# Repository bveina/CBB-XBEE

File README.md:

CBB-XBEE
========

This repository contains the design files for the Logic Supply CBB-XBEE Cape for the 
BeagleBone and BeagleBone Black. It's a general prototyping cape with a footprint to connect a XBee or
other compatible radio module.

The CBB-XBEE Cape is available at http://www.logicsupply.com/components/beaglebone/capes/cbb-xbee/

Check out the CBB-XBEE manual at https://docs.google.com/document/d/1f1zFzsrbu90K2d8ETkYjHSfjAa8HdVvbnBUYrnl4jPE/edit?usp=sharing

----

Follow us on Google+ for updates and more information: https://plus.google.com/u/0/b/103613886667848850929/

Created by Alexander Hiam for Logic Supply.

This work is licensed under the Creative Commons Attribution-Share Alike 3.0 Unported License. 
To view a copy of this license, visit http://creativecommons.org/licenses/by-sa/3.0/ or send a 
letter to Creative Commons, 171 Second Street, Suite 300, San Francisco, California, 94105, USA.

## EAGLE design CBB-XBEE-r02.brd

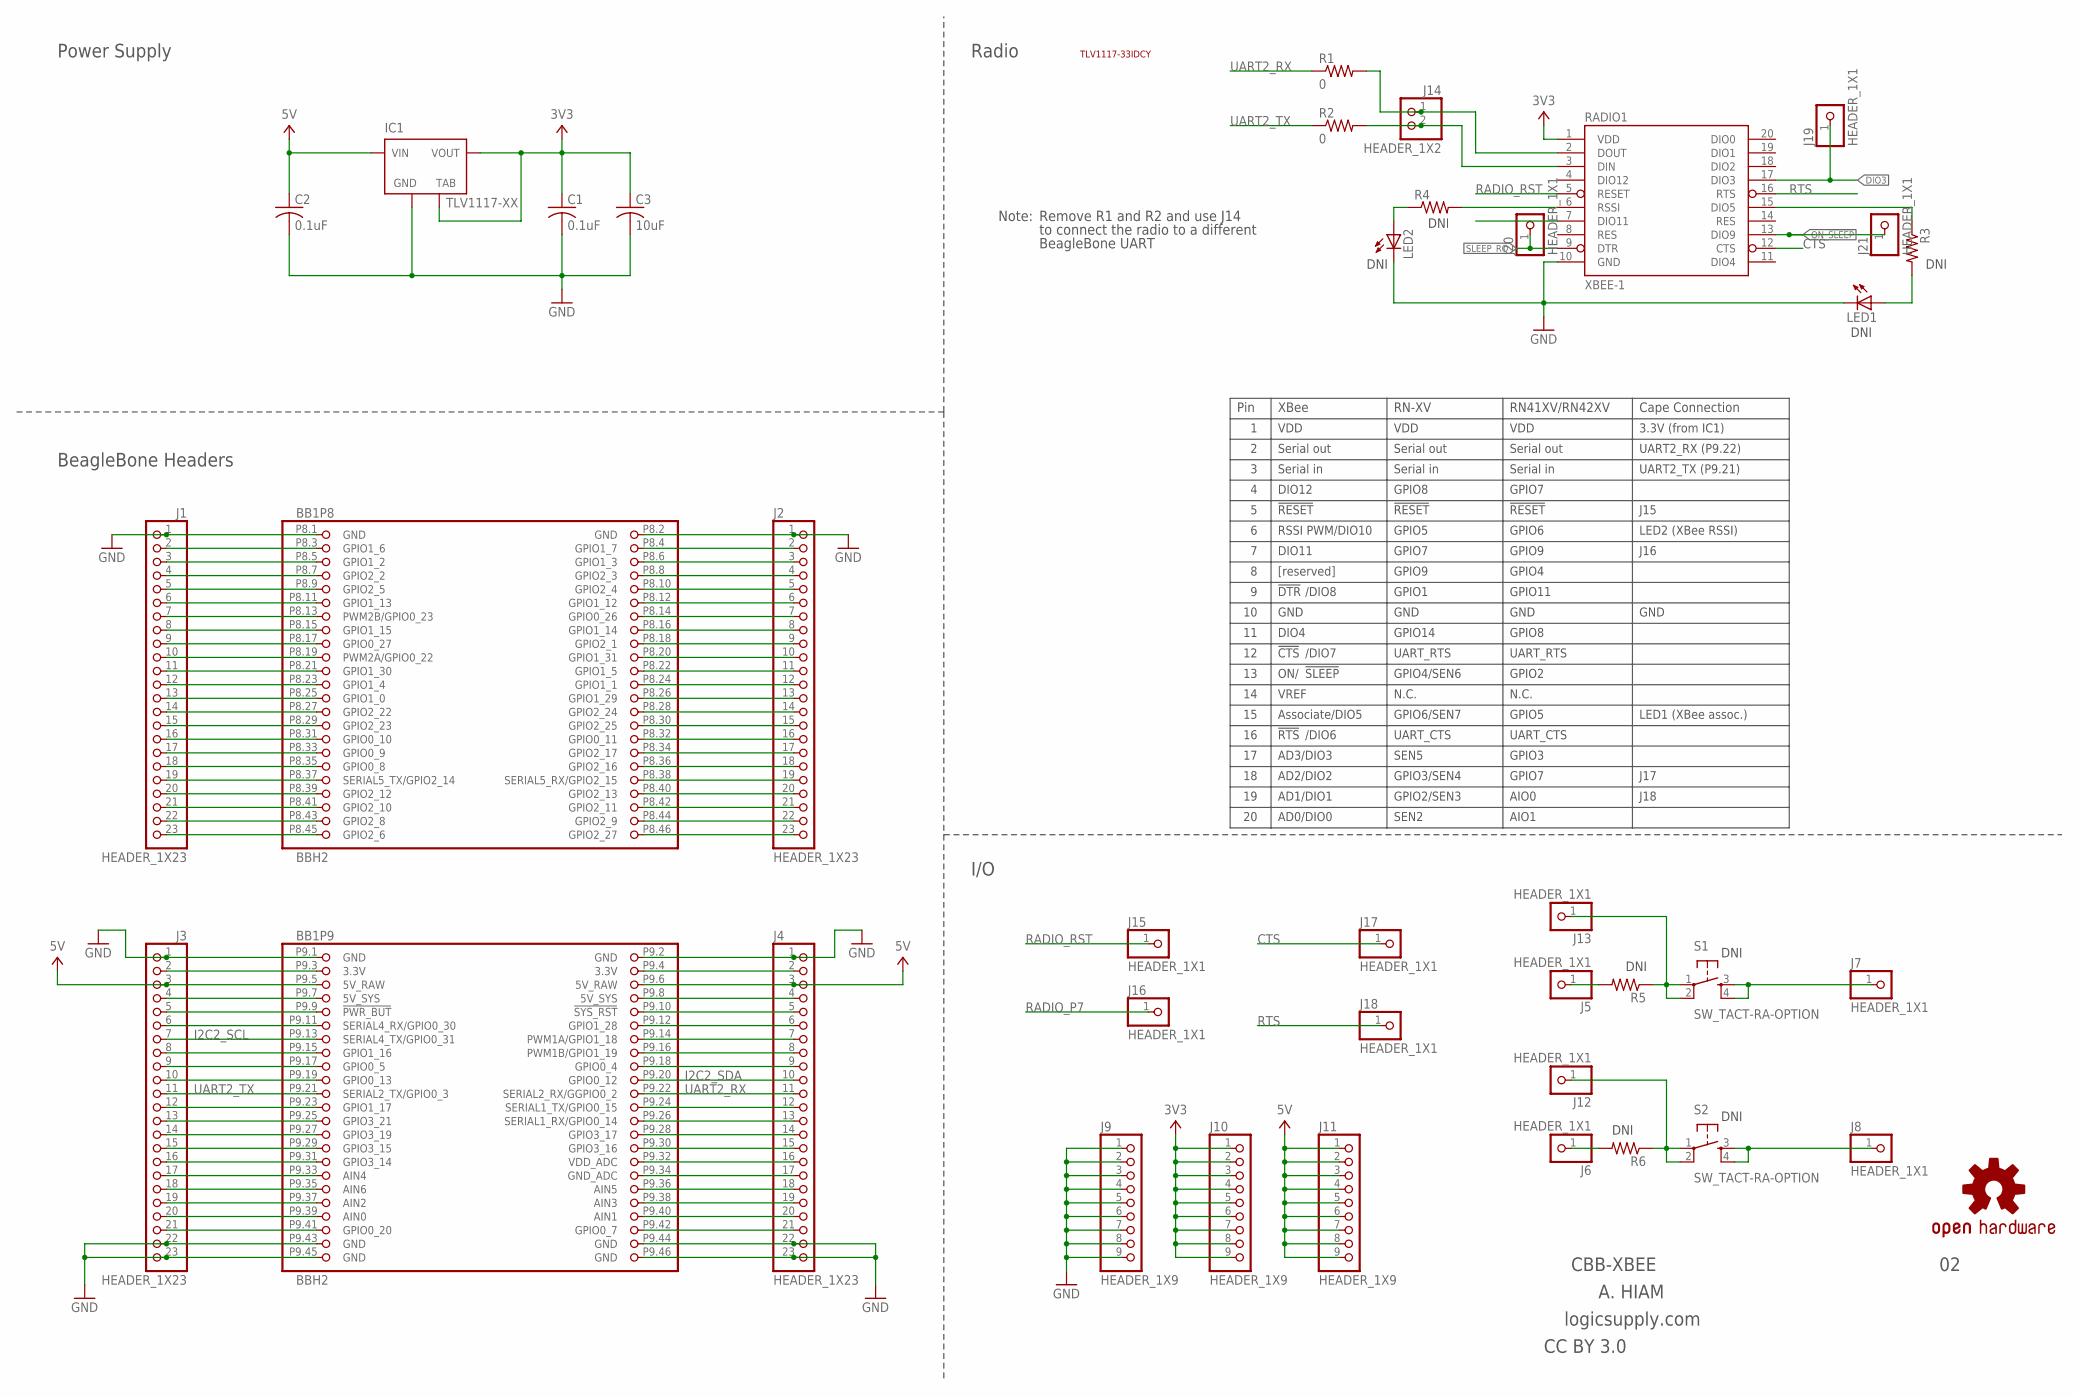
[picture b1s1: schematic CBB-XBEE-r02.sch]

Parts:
BB1: BBH2; BB_CAPE_TOP
C1, C2: 0.1uF; C0805
C3: 10uF; C0805
IC1: TLV1117-XX; SOT223
J1, J2, J3, J4: HEADER_1X23
J5, J6, J7, J8, J12, J13, J15, J16, J17, J18, J19, J20, J21: HEADER_1X1
J9, J10, J11: HEADER_1X9
J14: HEADER_1X2
LED1, LED2: LEDCHIPLED_0805; CHIPLED_0805
R1, R2: 0; R0805
R3, R4: R0805
R5, R6: R0207/10; 0207/10
RADIO1: XBEE-1; XBEE
S1, S2: SW_TACT-RA-OPTION; TACT-PTH-RA-OPTION
U$7: OSHW-LOGOM; OSHW-LOGO-M

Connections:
3V3: C1.1, C3.1, IC1.2 (VOUT), IC1.4 (TAB), J10.1, J10.2, J10.3, J10.4, J10.5, J10.6, J10.7, J10.8, J10.9, RADIO1.1 (VDD)
5V: BB1.P9.5 (5V_RAW), BB1.P9.6 (5V_RAW), C2.1, IC1.3 (VIN), J3.3, J4.3, J11.1, J11.2, J11.3, J11.4, J11.5, J11.6, J11.7, J11.8, J11.9
CTS: J17.1, RADIO1.12 (CTS)
DIO3: J19.1, RADIO1.17 (DIO3)
GND: BB1.P8.1 (GND), BB1.P8.2 (GND), BB1.P9.1 (GND), BB1.P9.2 (GND), BB1.P9.43 (GND), BB1.P9.44 (GND), BB1.P9.45 (GND), BB1.P9.46 (GND), C1.2, C2.2, C3.2, IC1.1 (GND), J1.1, J2.1, J3.1, J3.22, J3.23, J4.1, J4.22, J4.23, J9.1, J9.2, J9.3, J9.4, J9.5, J9.6, J9.7, J9.8, J9.9, LED1.C, LED2.C, RADIO1.10 (GND)
I2C2_SCL: BB1.P9.19 (GPIO0_13), J3.10
I2C2_SDA: BB1.P9.20 (GPIO0_12), J4.10
unnamed: BB1.P9.14 (PWM1A/GPIO1_18), J4.7
unnamed: BB1.P8.3 (GPIO1_6), J1.2
unnamed: BB1.P8.5 (GPIO1_2), J1.3
unnamed: BB1.P8.7 (GPIO2_2), J1.4
unnamed: BB1.P8.9 (GPIO2_5), J1.5
unnamed: BB1.P8.11 (GPIO1_13), J1.6
unnamed: BB1.P8.13 (PWM2B/GPIO0_23), J1.7
unnamed: BB1.P8.15 (GPIO1_15), J1.8
unnamed: BB1.P8.17 (GPIO0_27), J1.9
unnamed: BB1.P8.19 (PWM2A/GPIO0_22), J1.10
unnamed: BB1.P8.21 (GPIO1_30), J1.11
unnamed: BB1.P8.23 (GPIO1_4), J1.12
unnamed: R3.1, RADIO1.15 (DIO5)
unnamed: BB1.P9.3 (3.3V), J3.2
unnamed: BB1.P9.4 (3.3V), J4.2
unnamed: BB1.P8.25 (GPIO1_0), J1.13
unnamed: BB1.P8.27 (GPIO2_22), J1.14
unnamed: BB1.P8.29 (GPIO2_23), J1.15
unnamed: BB1.P8.31 (GPIO0_10), J1.16
unnamed: BB1.P8.33 (GPIO0_9), J1.17
unnamed: BB1.P8.35 (GPIO0_8), J1.18
unnamed: BB1.P8.37 (SERIAL5_TX/GPIO2_14), J1.19
unnamed: BB1.P8.39 (GPIO2_12), J1.20
unnamed: BB1.P8.41 (GPIO2_10), J1.21
unnamed: BB1.P8.43 (GPIO2_8), J1.22
unnamed: BB1.P8.45 (GPIO2_6), J1.23
unnamed: J13.1, R5.1, S1.1, S1.2
unnamed: BB1.P9.10 (!SYS_RST), J4.5
unnamed: R4.2, RADIO1.6 (RSSI)
unnamed: LED1.A, R3.2
unnamed: BB1.P9.16 (PWM1B/GPIO1_19), J4.8
unnamed: BB1.P9.18 (GPIO0_4), J4.9
unnamed: BB1.P9.7 (5V_SYS), J3.4
unnamed: BB1.P9.24 (SERIAL1_TX/GPIO0_15), J4.12
unnamed: BB1.P9.26 (SERIAL1_RX/GPIO0_14), J4.13
unnamed: BB1.P9.28 (GPIO3_17), J4.14
unnamed: BB1.P9.30 (GPIO3_16), J4.15
unnamed: BB1.P9.32 (VDD_ADC), J4.16
unnamed: BB1.P9.34 (GND_ADC), J4.17
unnamed: BB1.P9.36 (AIN5), J4.18
unnamed: BB1.P9.38 (AIN3), J4.19
unnamed: BB1.P9.40 (AIN1), J4.20
unnamed: BB1.P9.42 (GPIO0_7), J4.21
unnamed: J12.1, R6.1, S2.1, S2.2
unnamed: J8.1, S2.3, S2.4
unnamed: J7.1, S1.3, S1.4
unnamed: BB1.P9.8 (5V_SYS), J4.4
unnamed: J5.1, R5.2
unnamed: BB1.P9.9 (!PWR_BUT), J3.5
unnamed: BB1.P9.11 (SERIAL4_RX/GPIO0_30), J3.6
unnamed: BB1.P9.13 (SERIAL4_TX/GPIO0_31), J3.7
unnamed: BB1.P9.15 (GPIO1_16), J3.8
unnamed: BB1.P9.17 (GPIO0_5), J3.9
unnamed: J6.1, R6.2
unnamed: BB1.P9.23 (GPIO1_17), J3.12
unnamed: BB1.P9.25 (GPIO3_21), J3.13
unnamed: BB1.P9.27 (GPIO3_19), J3.14
unnamed: BB1.P9.29 (GPIO3_15), J3.15
unnamed: BB1.P9.31 (GPIO3_14), J3.16
unnamed: BB1.P9.33 (AIN4), J3.17
unnamed: BB1.P9.35 (AIN6), J3.18
unnamed: BB1.P9.37 (AIN2), J3.19
unnamed: BB1.P9.39 (AIN0), J3.20
unnamed: BB1.P9.41 (GPIO0_20), J3.21
unnamed: BB1.P8.4 (GPIO1_7), J2.2
unnamed: BB1.P8.6 (GPIO1_3), J2.3
unnamed: BB1.P8.8 (GPIO2_3), J2.4
unnamed: BB1.P8.10 (GPIO2_4), J2.5
unnamed: BB1.P8.12 (GPIO1_12), J2.6
unnamed: BB1.P8.14 (GPIO0_26), J2.7
unnamed: BB1.P8.16 (GPIO1_14), J2.8
unnamed: BB1.P8.18 (GPIO2_1), J2.9
unnamed: BB1.P8.20 (GPIO1_31), J2.10
unnamed: BB1.P8.22 (GPIO1_5), J2.11
unnamed: BB1.P8.24 (GPIO1_1), J2.12
unnamed: BB1.P8.26 (GPIO1_29), J2.13
unnamed: BB1.P8.28 (GPIO2_24), J2.14
unnamed: BB1.P8.30 (GPIO2_25), J2.15
unnamed: BB1.P8.32 (GPIO0_11), J2.16
unnamed: BB1.P8.34 (GPIO2_17), J2.17
unnamed: BB1.P8.36 (GPIO2_16), J2.18
unnamed: BB1.P8.38 (SERIAL5_RX/GPIO2_15), J2.19
unnamed: BB1.P8.40 (GPIO2_13), J2.20
unnamed: BB1.P8.42 (GPIO2_11), J2.21
unnamed: BB1.P8.44 (GPIO2_9), J2.22
unnamed: BB1.P8.46 (GPIO2_27), J2.23
unnamed: LED2.A, R4.1
unnamed: J14.2, R2.2, RADIO1.3 (DIN)
unnamed: J14.1, R1.2, RADIO1.2 (DOUT)
unnamed: BB1.P9.12 (GPIO1_28), J4.6
ON_!SLEEP: J21.1, RADIO1.13 (DIO9)
RADIO_P7: J16.1, RADIO1.7 (DIO11)
RADIO_RST: J15.1, RADIO1.5 (RESET)
RTS: J18.1, RADIO1.16 (RTS)
SLEEP_RQ: J20.1, RADIO1.9 (DTR)
UART2_RX: BB1.P9.22 (SERIAL2_RX/GGPIO0_2), J4.11, R1.1
UART2_TX: BB1.P9.21 (SERIAL2_TX/GPIO0_3), J3.11, R2.1

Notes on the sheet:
CBB-XBEE
A. HIAM
BeagleBone Headers
CC BY 3.0
XBee
RN-XV
RN41XV/RN42XV
Pin
VDD
GND
Serial out
Serial in
Cape Connection
3.3V (from IC1)
DIO12
!RESET
RSSI PWM/DIO10
DIO11
[reserved]
!DTR
/DIO8
DIO4
!CTS
!RTS
/DIO7
/DIO6
VREF
ON/
!SLEEP
Associate/DIO5
AD3/DIO3
AD2/DIO2
AD1/DIO1
AD0/DIO0
GPIO8
GPIO5
GPIO7
GPIO9
GPIO1
GPIO14

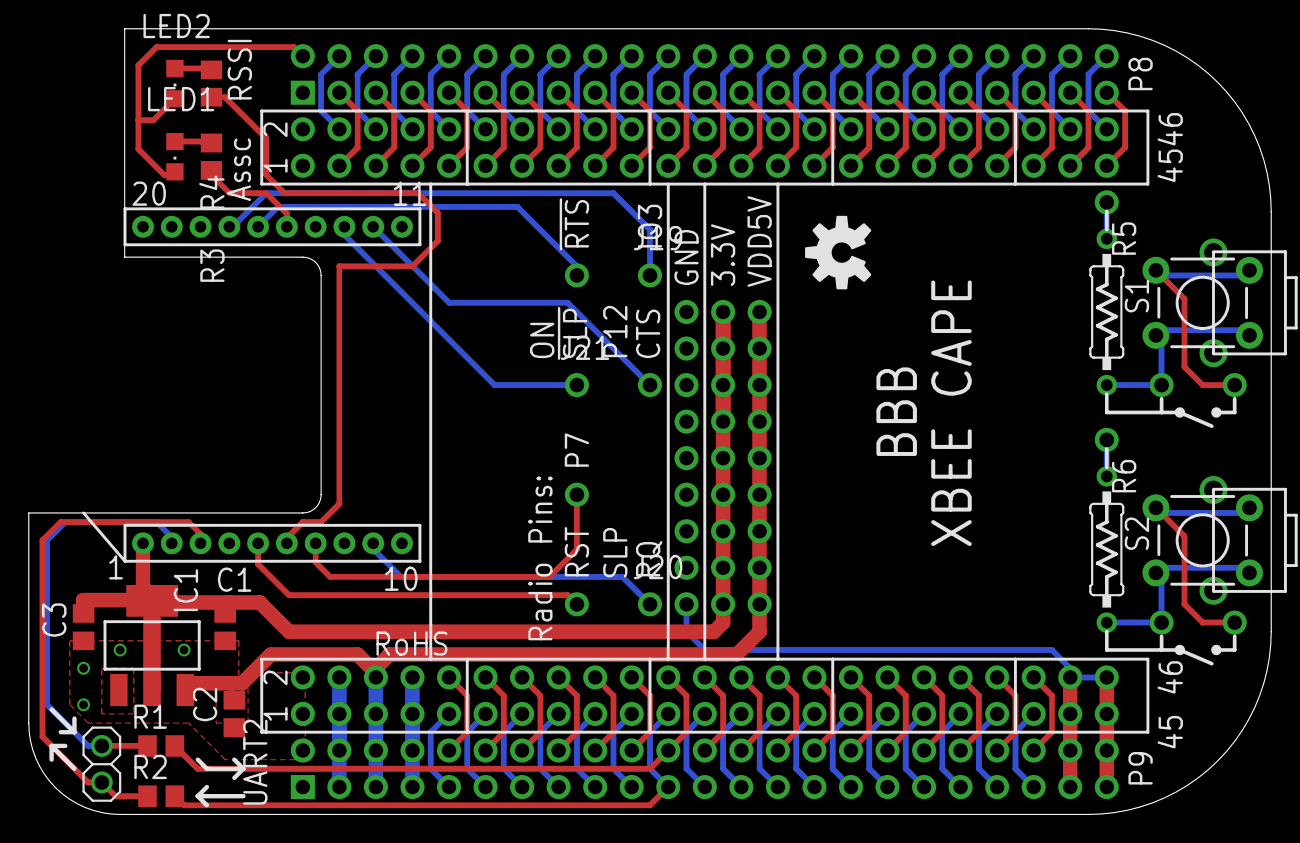
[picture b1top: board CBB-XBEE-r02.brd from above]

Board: 2 copper layers, 86.4 x 54.6 mm, 38 parts (1 on the bottom side), 104 nets.

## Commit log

2014-06-03 README
2014-06-03 added schematic
2016-06-06 Uploaded Eagle files
2020-10-29 modified layout to include extra test points for series 3 xbees.
